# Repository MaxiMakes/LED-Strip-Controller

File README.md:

# LED-Strip-Controller
Design/Firmware in progress

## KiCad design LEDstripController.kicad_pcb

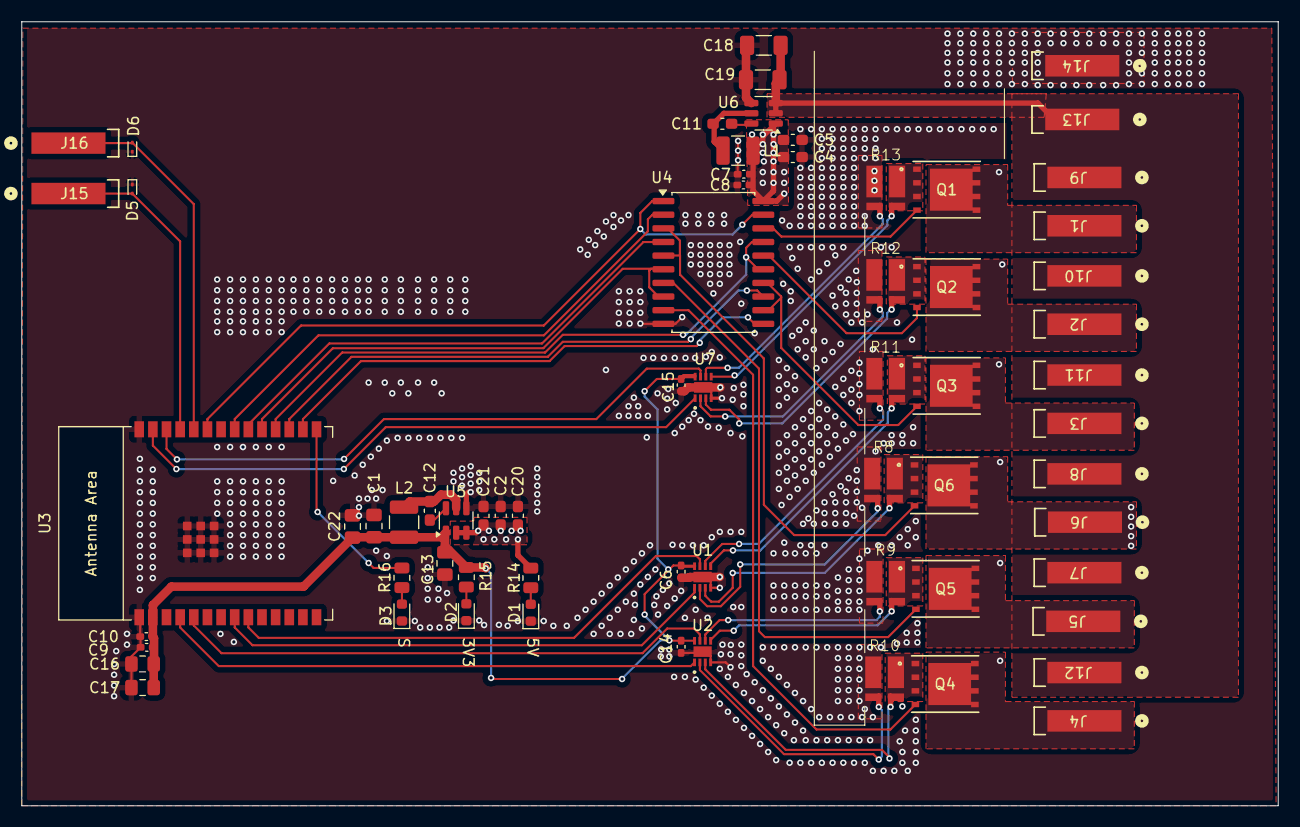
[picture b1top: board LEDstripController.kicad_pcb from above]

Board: 2 copper layers, 117.0 x 73.0 mm, 78 parts (0 on the bottom side), 57 nets.

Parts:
C1, C13, C16, C17, C22: 22uF 6.3V; C_0805_2012Metric_Pad1.18x1.45mm_HandSolder
C2, C4, C5, C20, C21: 22uF 10V; C_0603_1608Metric_Pad1.08x0.95mm_HandSolder
C6, C7, C10, C14, C15: 0.1uF 16V; C_0402_1005Metric_Pad0.74x0.62mm_HandSolder
C8, C9: 1uF 16V; C_0402_1005Metric_Pad0.74x0.62mm_HandSolder
C11, C12: 0.1uF 50V; C_0603_1608Metric_Pad1.08x0.95mm_HandSolder
C18, C19: 10uF 50V; C_1206_3216Metric_Pad1.33x1.80mm_HandSolder
D1, D2: 150060GS75000; LED_0603_1608Metric
D3: 150060BS75000; LED_0603_1608Metric
D5, D6: ESD9B3.3ST5G; D_SOD-923
J1, J2, J3, J4, J5, J6, J7, J8, J9, J10, J11, J12, J13, J14, J15, J16: 2065-100/998-403; CONN_2065-100&slash_998-403_WAG
L1, L2: 4.7uH; L_1210_3225Metric
NT1, NT2, NT3, NT4, NT5, NT6, NT7, NT8, NT9, NT10, NT11, NT12: NetTie_2; NetTie-2_SMD_Pad0.5mm
Q1, Q2, Q3, Q4, Q5, Q6: SIR500DP-T1-RE3; MOSFET_DP-T1-RE3_VIS_fix
R8, R9, R10, R11, R12, R13: 0.2mR 3W 1%; wsk1216_shunt
R14: 470R; R_0805_2012Metric
R15: 82R; R_0805_2012Metric
R16: 33R; R_0805_2012Metric
U1, U2, U7: INA2180A3IDSGR; WSON8_DSG_TEX
U3: ESP32-C6-WROOM-1
U4: SN74LS244DWR; SOIC-20W_7.5x12.8mm_P1.27mm
U5: AP63203WU; TSOT-23-6
U6: AP63205WU; TSOT-23-6

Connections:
+3.3V: C1.1, C6.1, C9.1, C10.1, C13.1, C14.1, C15.1, C16.1, C17.1, C22.1, L2.2, R15.1, U1.8 (VS), U2.8 (VS), U3.2 (3V3), U5.1 (FB), U7.8 (VS)
+5V: C2.1, C4.1, C5.1, C7.1, C8.1, C20.1, C21.1, L1.2, R14.1, U4.20 (VCC), U5.2 (EN), U5.3 (IN), U6.1 (FB)
/LED_Driver/O1: J1.1, Q1.5 (D)
/LED_Driver/O2: J2.1, Q2.5 (D)
/LED_Driver/O3: J3.1, Q3.5 (D)
/LED_Driver/O4: J4.1, Q4.5 (D)
/LED_Driver/O5: J5.1, Q5.5 (D)
/LED_Driver/O6: J6.1, Q6.5 (D)
AIN0: U1.1 (OUT1), U3.8 (GPIO0/ADC1_CH0/XTAL_32K_P)
AIN1: U1.7 (OUT2), U3.9 (GPIO1/ADC1_CH1/XTAL_32K_N)
AIN2: U3.27 (GPIO2/ADC1_CH2), U7.1 (OUT1)
AIN3: U3.26 (GPIO3/ADC1_CH3), U7.7 (OUT2)
AIN4: U2.1 (OUT1), U3.4 (MTMS/GPIO4/ADC1_CH4)
AIN5: U2.7 (OUT2), U3.5 (MTDI/GPIO5/ADC1_CH5)
GND: C1.2, C2.2, C4.2, C5.2, C6.2, C7.2, C8.2, C9.2, C10.2, C13.2, C14.2, C15.2, C16.2, C17.2, C18.2, C19.2, C20.2, C21.2, C22.2, D1.1 (K), D2.1 (K), D3.1 (K), D5.1 (A1), D6.1 (A1), J14.1, NT2.1, NT3.1, NT4.1, NT5.1, NT6.1, NT7.2, R8.2, R9.2, R10.2, R11.2, R12.2, R13.2, U1.4 (GND), U1.9 (GND), U2.4 (GND), U2.9 (GND), U3.1 (GND), U3.28 (GND), U3.29 (GND), U4.10 (GND), U5.4 (GND), U6.4 (GND), U7.4 (GND), U7.9 (GND)
LED_PWM1: U3.16 (GPIO18), U4.11
LED_PWM2: U3.17 (GPIO19), U4.13
LED_PWM3: U3.18 (GPIO20), U4.15, U4.17
LED_PWM4: U3.19 (GPIO21), U4.6, U4.8
LED_PWM5: U3.20 (GPIO22), U4.4
LED_PWM6: U3.21 (GPIO23), U4.2
unnamed: D1.2 (A), R14.2
unnamed: D2.2 (A), R15.2
unnamed: D3.2 (A), R16.2
unnamed: NT1.2, Q6.1 (S), Q6.2 (S), Q6.3 (S), R8.1
unnamed: NT8.2, Q5.1 (S), Q5.2 (S), Q5.3 (S), R9.1
unnamed: NT9.2, Q4.1 (S), Q4.2 (S), Q4.3 (S), R10.1
unnamed: NT10.2, Q3.1 (S), Q3.2 (S), Q3.3 (S), R11.1
unnamed: NT11.2, Q1.1 (S), Q1.2 (S), Q1.3 (S), R13.1
unnamed: NT12.1, Q2.1 (S), Q2.2 (S), Q2.3 (S), R12.1
unnamed: Q1.4 (G), U4.18
unnamed: Q2.4 (G), U4.16
unnamed: Q3.4 (G), U4.12, U4.14
unnamed: Q4.4 (G), U4.9
unnamed: Q5.4 (G), U4.7
unnamed: Q6.4 (G), U4.3, U4.5
unnamed: C12.2, U5.6 (BST)
unnamed: C12.1, L2.1, U5.5 (SW)
unnamed: C11.2, U6.6 (BST)
unnamed: C11.1, L1.1, U6.5 (SW)
R1+: NT11.1, U7.5 (IN+2)
R1-: NT2.2, U7.6 (IN-2)
R2+: NT12.2, U7.3 (IN+1)
R2-: NT3.2, U7.2 (IN-1)
R3+: NT10.1, U1.5 (IN+2)
R3-: NT4.2, U1.6 (IN-2)
R4+: NT9.1, U2.3 (IN+1)
R4-: NT5.2, U2.2 (IN-1)
R5+: NT8.1, U2.5 (IN+2)
R5-: NT6.2, U2.6 (IN-2)
R6+: NT1.1, U1.3 (IN+1)
R6-: NT7.1, U1.2 (IN-1)
RX0: D6.2 (A2), J16.1, U3.24 (U0RXD/GPIO17)
STATUS_LED: R16.1, U3.15 (GPIO9)
TX0: D5.2 (A2), J15.1, U3.25 (U0TXD/GPIO16)
VCC: C18.1, C19.1, J7.1, J8.1, J9.1, J10.1, J11.1, J12.1, J13.1, U6.2 (EN), U6.3 (IN)
~LED_EN: U3.23 (GPIO15), U4.1, U4.19

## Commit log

2024-08-24 init
